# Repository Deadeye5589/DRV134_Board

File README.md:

# DRV134_Board
AUX to XLR converter based on the DRV134 chipset

This board can be used to generate a differential audio signal for class D amplifieres like 125ASX2 form a single ended audio input.
PCBs can be ordered at JLCPCB directly with the included Gerber files.

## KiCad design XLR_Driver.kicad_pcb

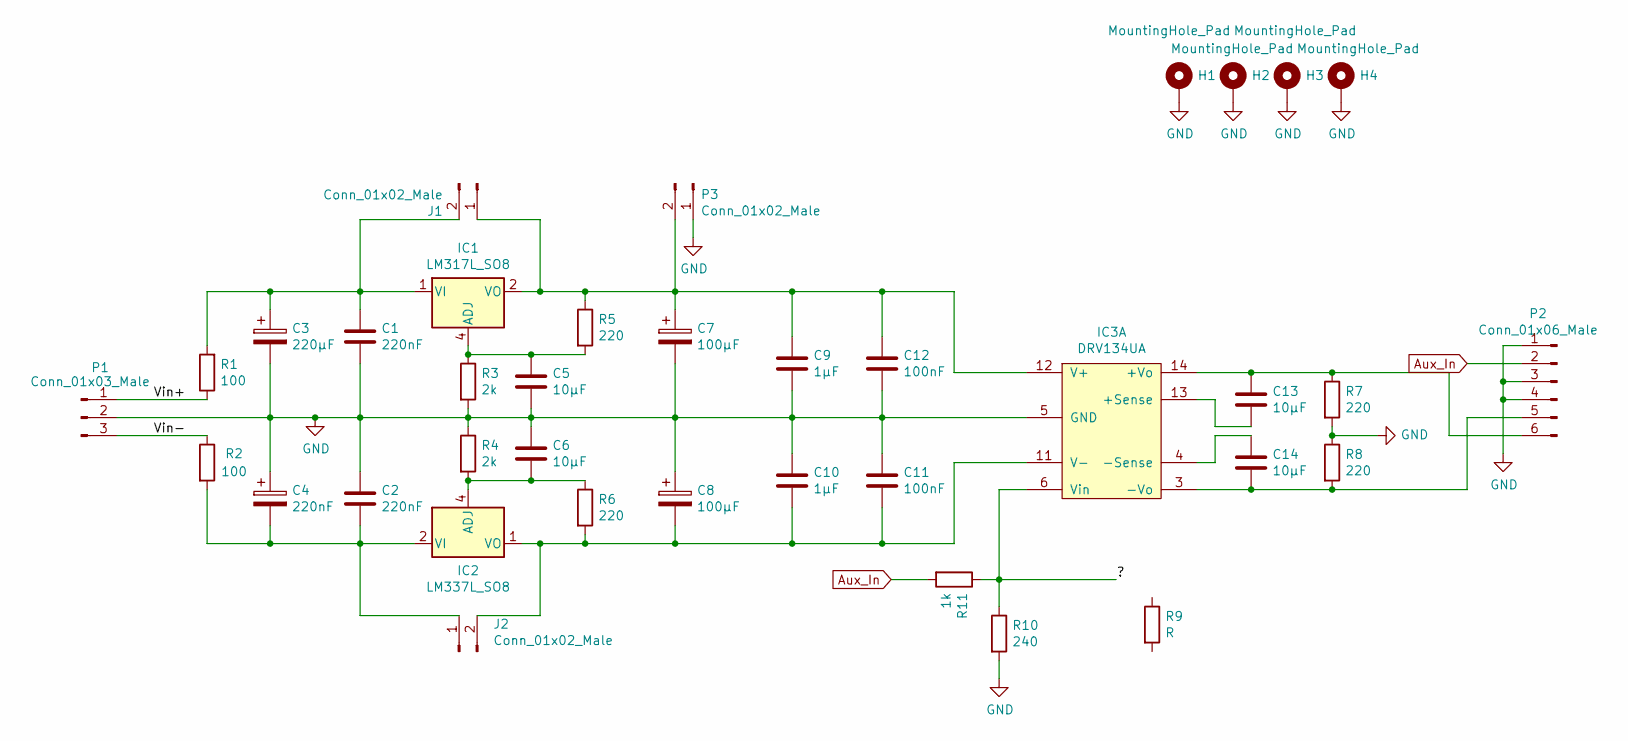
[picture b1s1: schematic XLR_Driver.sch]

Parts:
C1, C2: 220nF; C_0805_2012Metric_Pad1.15x1.40mm_HandSolder
C3: 220µF; CP_Elec_8x10.5
C4: 220nF; CP_Elec_8x10.5
C5, C6, C13, C14: 10µF; C_0805_2012Metric_Pad1.15x1.40mm_HandSolder
C7, C8: 100µF; CP_Elec_6.3x5.8
C9, C10: 1µF; C_0805_2012Metric_Pad1.15x1.40mm_HandSolder
C11, C12: 100nF; C_0805_2012Metric_Pad1.15x1.40mm_HandSolder
H1, H2, H3, H4: MountingHole_Pad; MountingHole_3.2mm_M3_ISO14580_Pad
IC1: LM317L_SO8; SOIC-8_3.9x4.9mm_P1.27mm
IC2: LM337L_SO8; SOIC-8_3.9x4.9mm_P1.27mm
IC3: DRV134UA; SOIC127P1030X265-16N
J1, J2: Conn_01x02_Male; PinHeader_1x02_P2.54mm_Vertical
P1: Conn_01x03_Male; PinHeader_1x03_P2.54mm_Vertical
P2: Conn_01x06_Male; PinHeader_1x06_P2.54mm_Vertical
P3: Conn_01x02_Male; PinHeader_1x02_P2.54mm_Vertical
R1, R2: 100; R_0805_2012Metric_Pad1.15x1.40mm_HandSolder
R3, R4: 2k; R_0805_2012Metric_Pad1.15x1.40mm_HandSolder
R5, R6, R7, R8: 220; R_0805_2012Metric_Pad1.15x1.40mm_HandSolder
R9: R
R10: 240; R_0805_2012Metric_Pad1.15x1.40mm_HandSolder
R11: 1k; R_0805_2012Metric_Pad1.15x1.40mm_HandSolder

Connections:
/Vin+: P1.1, R1.1
/Vin-: P1.3, R2.1
Aux_In: P2.2, R11.2
GND: C1.2, C2.2, C3.2, C4.1, C5.2, C6.2, C7.2, C8.1, C9.2, C10.1, C11.1, C12.2, H1.1, H2.1, H3.1, H4.1, IC3.5 (GND), P1.2, P2.1, P2.3, P2.4, P3.1, R3.2, R4.1, R7.2, R8.1, R9.2, R10.2
unnamed: C1.1, C3.1, IC1.1 (VI), J1.2, R1.2
unnamed: C2.1, C4.2, IC2.2 (VI), IC2.3 (VI), IC2.6 (VI), IC2.7 (VI), J2.1, R2.2
unnamed: C5.1, IC1.4 (ADJ), R3.1, R5.2
unnamed: C6.1, IC2.4 (ADJ), R4.2, R6.1
unnamed: C8.2, C10.2, C11.2, IC2.1 (VO), IC3.11 (V-), J2.2, R6.2
unnamed: C7.1, C9.1, C12.1, IC1.2 (VO), IC1.3 (VO), IC1.6 (VO), IC1.7 (VO), IC3.12 (V+), J1.1, P3.2, R5.1
unnamed: C13.1, IC3.14 (+Vo), P2.6, R7.1
unnamed: C13.2, IC3.13 (+Sense)
unnamed: C14.1, IC3.4 (-Sense)
unnamed: C14.2, IC3.3 (-Vo), P2.5, R8.2
unnamed: IC3.6 (Vin), R9.1, R10.1, R11.1

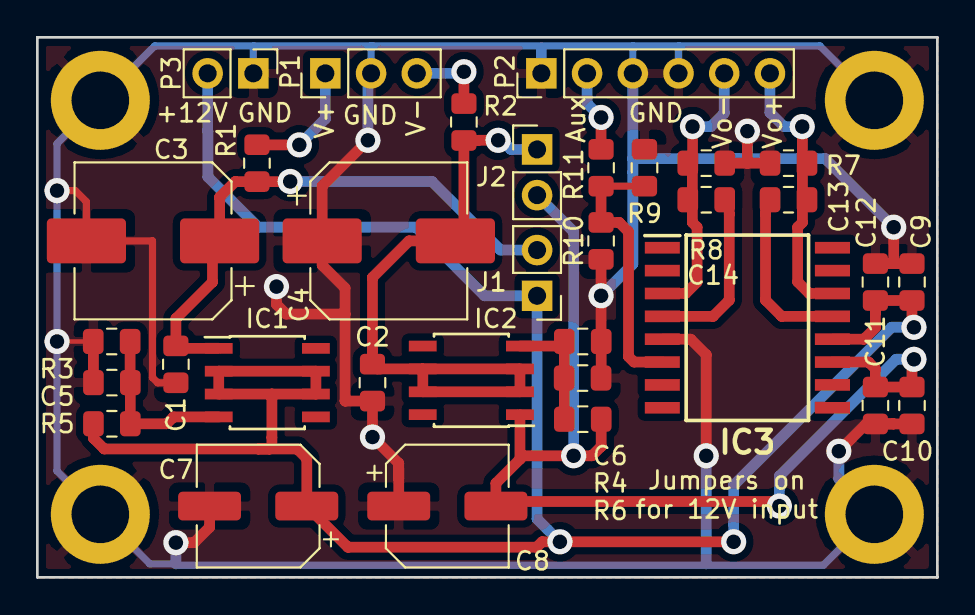
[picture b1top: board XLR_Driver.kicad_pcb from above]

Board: 2 copper layers, 50.0 x 30.0 mm, 37 parts (0 on the bottom side), 15 nets.

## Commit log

2019-07-30 Final connections missing
2020-11-02 V1.0 release
    Completed circuit
    Ready to order PCBs
2020-11-02 V1.0 release
    Data ready
    Can be ordered directly at JLCPCB
2020-11-02 V1 release
    Matching BOM for V1 release
